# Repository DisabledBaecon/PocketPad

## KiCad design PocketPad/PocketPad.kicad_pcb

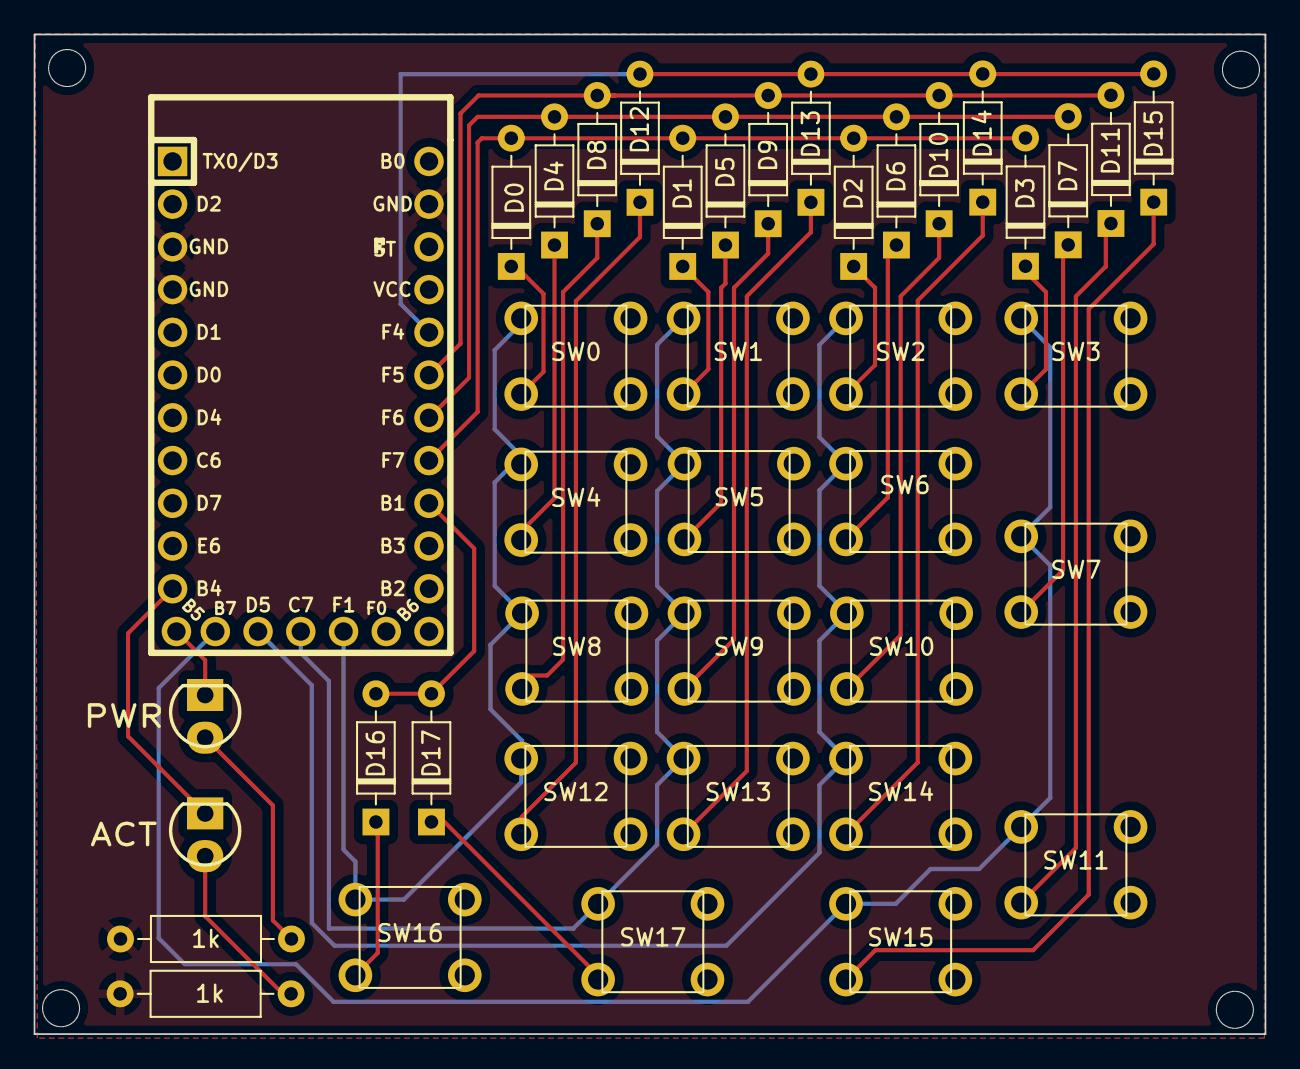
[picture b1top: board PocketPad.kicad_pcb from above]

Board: 2 copper layers, 73.2 x 59.4 mm, 41 parts (0 on the bottom side), 32 nets.

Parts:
ACT: LED; LED_3mm
ACT-R1: 1k; R_Axial_DIN0207_L6.3mm_D2.5mm_P10.16mm_Horizontal
D0, D1, D2, D3, D4, D5, D6, D7, D8, D9, D10, D11, D12, D13, D14, D15, D16, D17: DIODE; D_DO-35_SOD27_P7.62mm_Horizontal
MCU1: Elite-C
PWR: LED; LED_3mm
PWR-R1: 1k; R_Axial_DIN0207_L6.3mm_D2.5mm_P10.16mm_Horizontal
SW0, SW1, SW2, SW3, SW4, SW5, SW6, SW7, SW8, SW9, SW10, SW11, SW12, SW13, SW14, SW15, SW16, SW17: SW_THT_6x6; Switch_THT_6x6x8.5

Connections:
COL0: MCU1.28 (F1), SW0.1, SW4.1, SW8.1, SW12.1, SW16.1
COL1: MCU1.27 (C7), SW1.1, SW5.1, SW9.1, SW13.1, SW17.1
COL2: MCU1.26 (D5), SW2.1, SW6.1, SW10.1, SW14.1
COL3: MCU1.25 (B7), SW3.1, SW7.1, SW11.1, SW15.1
GND: ACT-R1.2, MCU1.3 (GND), MCU1.4 (GND), MCU1.23 (GND), PWR-R1.1
unnamed: ACT.2 (A), MCU1.11 (8/PB4)
unnamed: ACT.1 (K), ACT-R1.1
unnamed: D6.1 (A), SW6.3
unnamed: MCU1.12 (9/PB5), PWR.2 (A)
unnamed: PWR.1 (K), PWR-R1.2
unnamed: D0.1 (A), SW0.3
unnamed: D1.1 (A), SW1.3
unnamed: D2.1 (A), SW2.3
unnamed: D3.1 (A), SW3.3
unnamed: D4.1 (A), SW4.3
unnamed: D5.1 (A), SW5.3
unnamed: D7.1 (A), SW7.3
unnamed: D8.1 (A), SW8.3
unnamed: D9.1 (A), SW9.3
unnamed: D10.1 (A), SW10.3
unnamed: D11.1 (A), SW11.3
unnamed: D12.1 (A), SW12.3
unnamed: D13.1 (A), SW13.3
unnamed: D14.1 (A), SW14.3
unnamed: D15.1 (A), SW15.3
unnamed: D16.1 (A), SW16.3
unnamed: D17.1 (A), SW17.3
ROW0: D0.2 (K), D1.2 (K), D2.2 (K), D3.2 (K), MCU1.17 (A0/PF7)
ROW1: D4.2 (K), D5.2 (K), D6.2 (K), D7.2 (K), MCU1.18 (A1/PF6)
ROW2: D8.2 (K), D9.2 (K), D10.2 (K), D11.2 (K), MCU1.19 (A2/PF5)
ROW3: D12.2 (K), D13.2 (K), D14.2 (K), D15.2 (K), MCU1.20 (A3/PF4)
ROW4: D16.2 (K), D17.2 (K), MCU1.16 (15/PB1)

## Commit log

2022-11-29 Created kiCAD files
2022-11-30 Started project
2022-11-30 Replaced Diodes. Added 3D models
2022-11-30 V0.1 Complete
2022-11-30 Added GND plane
2022-11-30 Added edgecut with mounting holes
2022-11-30 Mounting Holes
2022-11-30 Edgecut expanded
2022-11-30 3D model adjustment
2022-11-30 Moved Mounting Holes
2022-11-30 edgecut replaced. Gerbers added
2022-11-30 Added Silkscreen
2022-11-30 Replaced Footprints and THT 3D Model
2022-11-30 Readded models and replaced footprint. Silkscreen done
2022-12-01 V0.2 : Removed SW18
    Redid trace routes. Removed SW18, moved SW16,17 over. Moved PWR & ACT LEDs
2022-12-01 symbols updated. PCB redone.
2022-12-01 V1 complete
2022-12-01 Deleted old Gerbers
2022-12-01 Update fp-info-cache
2022-12-01 Moved tracers, added gbr and drl
2022-12-01 Added 3D models
2022-12-01 Updated Gerbers
2022-12-04 backups update
2022-12-06 Adjusted placement of switches and trace routes
    Overall size reduced
2022-12-06 uploaded latest save
2022-12-06 Updated Gerbers. Added new keycap model
2022-12-06 Ummm
2022-12-07 backups
2022-12-07 File structure updated
